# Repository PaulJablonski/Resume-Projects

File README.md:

# Projects
Projects that are a part of my independent studies accompanied by my resume.

**Currently Includes:**
1. ***Android Embedded Security System*** - Manual object-detecting Android application meant for security applications, detects, isolates, and labels people in camera feed utilizing manual DB-scanning, k-means color processing, and image calibration techniques.
2. ***Granular Synthesizer*** - Custom VST3 plugin that allows for the granularization of instruments and audio in DAWs. Capable of performing time-stretching, pitch adjustment, randomization, alongside adjusting dryness/wetness, grain size, and grain density.
3. ***FPGA Soccer Heads*** - A recreation of a classic flash game that incorporated SystemVerilog and C onto a Microblaze FPGA board that was connected to peripheral devices such as a monitor and keyboard.
4. ***Handwritten Text Recognition*** - Classifies single hand-illustrated character from user's input using SVM and convolution, where both the back-end and front-end were created from scratch using Python3 (Full Stack).
5. ***Illini Harmonics*** - A GCP-hosted music-based social web app made with SQL, React, and Python for rating your listening history and sharing it with friends.
6. ***Laser & Voice Assisted Cat Toy*** - Autonomous cat toy capable of collision avoidance, treat dispensing, catch detection, and audio-based commands. Involved PCB development, custom CAD modelling for the shell, and Arduino programming for the toy's behavioral state machine.

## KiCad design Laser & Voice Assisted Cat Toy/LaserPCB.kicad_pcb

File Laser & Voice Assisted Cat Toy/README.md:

# Laser & Voice Assisted Cat Toy

**Description:**

This project involves a mouse-like toy, which has been seen before, but is now refined with multiple more advanced systems. The primary sensors consist of a distance measuring laser, a vibrational sensor, and a microphone in tandem with a miniature speaker. The first two serve in engaging the cat and improving both longevity and noise generation, whereas the final sensor system vastly improves user interaction through various voice commands. More specifically, the laser can be utilized to avoid collisions and detect ahead of the mouse, sparking movement changes that are more realistic for an animal. The vibrational sensor furthermore detects when the toy has been caught, which either dispenses a treat or plays dead depending on the toy's state. Finally, the aforementioned voice commands allow for the user to locate the toy at any time, or manually activate the toy itself without a need for physical contact.

Physically speaking, the non-rolling shape of a mouse also allows for more rigid and controllable movement. This is important for stabilizing the toy’s primary sensors and allows for greater reactivity to its environment and consequently less noisy behavior. The sensors as mentioned also are accompanied by several motorized and more physical systems. A moving tail is used to mimic the more excitatory behaviors of prey, making it more engaging than a typical toy's static tail. This is accompanied by faster motorized movements and more realistic movement states as is regulated by a microcontroller and stepper motor-driven wheel system. Further speaking, a latch can be controlled through a servo and used for dispensing treats from the back of the toy upon being caught. And finally, a rechargeable lithium ion battery is incorporated and regulated by a circuit protection system for easy re-usability.
 
The toy itself comprises four total subsystems:

* Sensor subsystem, including a VL53L1X laser sensor, an SW-420 vibration sensor, and a KY-038 sound sensor.
* Microcontroller subsystem, comprised of the ATmega328p, taking inputs from the sensor subsystem, and outputting to the motors and outputs subsystem.
* Motors and outputs subsystem, consisting of two Nema 17 short body motors, two SG90 servo motors, two A4988 stepper drivers, a PAM8302 sound amplifier, and one JSM 2.5mm speaker.
* Power subsystem, which has a 11.1V lithium-ion battery, three AZ1117 voltage regulators, and a CYT1091 button.

**Included Files:**

1. CAD - Includes all CAD files for the cat toy, including both versions of its main body, top and bottom panels, and its separate cover for treat dispensing that attaches to the toy's treat servo motor.
2. CatToyOverview.pdf - A comprehensive 26-page report that displays the results of this project, alongside more in-depth technical descriptions for each subsystem.
3. LaserPCB.kicad_pcb - KiCAD PCB file for the front-mounted PCB that contains the laser sensor.
4. MainPCB.kicad_pcb - KiCAD PCB file for the main system PCB that contains all other sensors and outputs, alongside the microcontroller and additional connections.
5. MainPCB.kicad_sch - KiCAD schematic file that compliments and provides the layed-out prototype for the aforementioned main PCB.
6. ToyFirmware.ino - Arduino code file that contains all states and operations of the toy's programmed behavior. This file serves as its primary state machine and is loaded onto the final version's ATmega328p controller.

**Demonstration Video (Click on image):**

<div align="center" style="position: relative; display: inline-block;">
  
</div>

**Honorable Mention Award:**

<p align="center">  
  Figure 1. Award for this project given by UIUC Professor Fang, placing within the top 7 projects among nearly 50 groups.
</p>

**Design Figures:**

<p align="center">  
  Figure 2. Initial concept sketch for the cat toy, including all intended functionalities.
</p>

<p align="center">  
  Figure 3. Initial concept render of disassembled front and back view of the toy.
</p>

<p align="center">  
  Figure 4. Finalized CAD model of the toy alongside its interior.
</p>

<p align="center">  
  Figure 5. Assembly of the final product, including buttons, sensors on the sides, holes for wheel mounts, power button, etc.
</p>

<p align="center">  
  Figure 6. Main PCB design, not including the connections made in final assembly.
</p>

<p align="center">  
  Figure 7. Laser PCB design, not including the connections made in final assembly.
</p>

<p align="center">  
  Figure 8. Functionality of motor operations in final toy, red LED representing directions, and green representing motor steps. Laser detection here demonstrates directional change.
</p>

<p align="center">  
  Figure 9. Vibration and treat dispensing functionality on display, treats are dispensed after three taps (catches).
</p>

**Block Diagrams:**

<p align="center">  
  Figure 10. Block diagram for overall subsystems and their connections.
</p>

<p align="center">  
  Figure 11. State machine that defines the general program behavior.
</p>

**Subsystem Schematic Figures:**

<p align="center">  
  Figure 12. Overall circuit schematic diagram.
</p>

<p align="center">  
  Figure 13. Sensor subsystem schematic diagram.
</p>

<p align="center">  
  Figure 14. Microcontroller subsystem schematic diagram.
</p>

<p align="center">  
  Figure 15. Motors & outputs subsystem schematic diagram.
</p>

<p align="center">  
  Figure 16. Power subsystem schematic diagram.
</p>

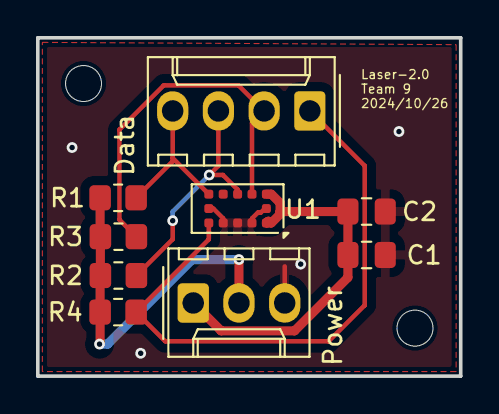
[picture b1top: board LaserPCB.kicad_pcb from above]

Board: 2 copper layers, 23.5 x 18.8 mm, 11 parts (0 on the bottom side), 7 nets.

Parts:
C1: 100nF; C_0805_2012Metric_Pad1.18x1.45mm_HandSolder
C2: 4.7uF; C_0805_2012Metric_Pad1.18x1.45mm_HandSolder
Data: Data; Molex_KK-254_AE-6410-04A_1x04_P2.54mm_Vertical
H1, H2: MountingHole; MountingHole_2mm
Power: Power; Molex_KK-254_AE-6410-03A_1x03_P2.54mm_Vertical
R1, R2, R3, R4: 10k; R_0805_2012Metric_Pad1.20x1.40mm_HandSolder
U1: VL53L1CXV0FY1; ST_VL53L1x

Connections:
/3.3V: C1.1, C2.1, Power.1, U1.1 (AVDDVCSEL), U1.11 (AVDD)
/GPIO1: Data.4, R1.2, U1.7 (GPIO1)
/IOVDD: Power.2, R1.1, R2.1, R3.1, R4.1
/SCL: Data.2, R3.2, U1.10 (SCL)
/SDA: Data.3, R2.2, U1.9 (SDA)
/XSHUT: Data.1, R4.2, U1.5 (XSHUT)
GND: C1.2, C2.2, Power.3, U1.2 (AVSSVCSEL), U1.3 (GND), U1.4 (GND), U1.6 (GND), U1.12 (GND)

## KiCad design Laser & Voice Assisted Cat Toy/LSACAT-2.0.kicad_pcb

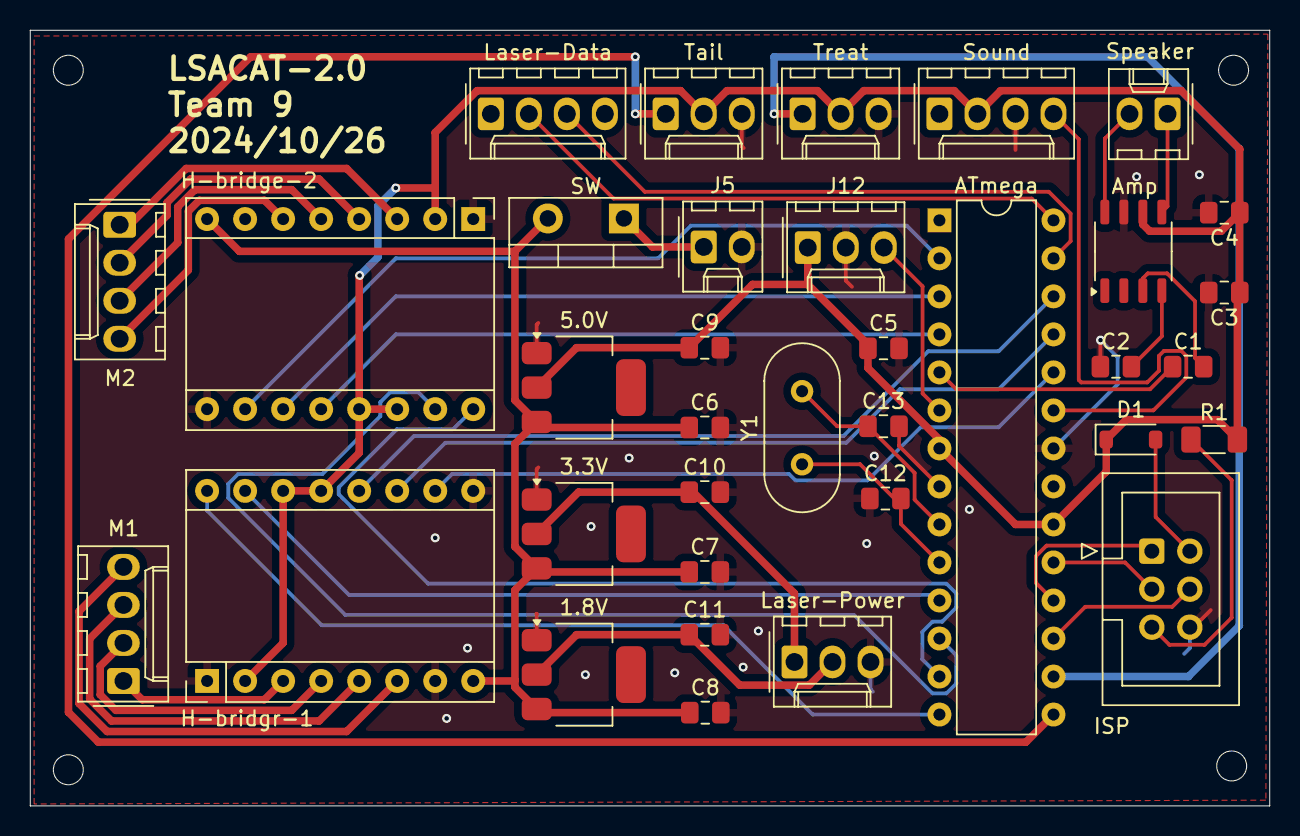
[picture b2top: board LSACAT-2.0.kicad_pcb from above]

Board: 2 copper layers, 82.8 x 51.8 mm, 39 parts (0 on the bottom side), 42 nets.

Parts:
1.8V: AZ1117-1.8; SOT-223
3.3V: AZ1117-3.3; SOT-223
5.0V: AZ1117-5.0; SOT-223
ATmega: ATmega328-P; DIP-28_W7.62mm
Amp: PAM8302AAS; SOP-8_3.9x4.9mm_P1.27mm
C1, C2: 0.1uF; C_0805_2012Metric_Pad1.18x1.45mm_HandSolder
C3: 10uF; C_0805_2012Metric_Pad1.18x1.45mm_HandSolder
C4, C5: 1uF; C_0805_2012Metric_Pad1.18x1.45mm_HandSolder
C6, C7, C8, C9, C10, C11: 22uF; C_0805_2012Metric_Pad1.18x1.45mm_HandSolder
C12, C13: 22pF; C_0805_2012Metric_Pad1.18x1.45mm_HandSolder
D1: MBR0520; D_SOD-123
H1, H2, H3, H4: MountingHole; MountingHole_2mm
H-bridge-2: A4988; Pololu_Breakout-16_15.2x20.3mm
H-bridgr-1: A4988; Pololu_Breakout-16_15.2x20.3mm
ISP: AVR-ISP-6; IDC-Header_2x03_P2.54mm_Vertical
J5: Battery; Molex_KK-254_AE-6410-02A_1x02_P2.54mm_Vertical
J12: SW-420; Molex_KK-254_AE-6410-03A_1x03_P2.54mm_Vertical
Laser-Data: Laser_Data; Molex_KK-254_AE-6410-04A_1x04_P2.54mm_Vertical
Laser-Power: Laser_Power; Molex_KK-254_AE-6410-03A_1x03_P2.54mm_Vertical
M1: M1; Molex_KK-254_AE-6410-04A_1x04_P2.54mm_Vertical
M2: M2; Molex_KK-254_AE-6410-04A_1x04_P2.54mm_Vertical
R1: 10k; R_1206_3216Metric_Pad1.30x1.75mm_HandSolder
SW: SW_Push; TO-220-2_Vertical
Sound: KY-038; Molex_KK-254_AE-6410-04A_1x04_P2.54mm_Vertical
Speaker: Speaker; Molex_KK-254_AE-6410-02A_1x02_P2.54mm_Vertical
Tail: Tail; Molex_KK-254_AE-6410-03A_1x03_P2.54mm_Vertical
Treat: Treat; Molex_KK-254_AE-6410-03A_1x03_P2.54mm_Vertical
Y1: 16Mhz; Crystal_HC49-U_Vertical

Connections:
/3.3V: 3.3V.2 (VO), C10.1, Laser-Power.1
/5V: 5.0V.2 (VO), ATmega.7 (VCC), ATmega.20 (AVCC), Amp.6 (VDD), C3.1, C4.1, C5.1, C9.1, D1.1 (K), H-bridge-2.2 (VDD), H-bridge-2.13 (~RESET), H-bridge-2.14 (~SLEEP), H-bridgr-1.2 (VDD), H-bridgr-1.13 (~RESET), H-bridgr-1.14 (~SLEEP), J12.1, R1.2, Sound.2, Tail.2, Treat.2
/11.1V: 1.8V.3 (VI), 3.3V.3 (VI), 5.0V.3 (VI), C6.1, C7.1, C8.1, H-bridge-2.8 (VMOT), H-bridgr-1.8 (VMOT), SW.2
/A1_M1: H-bridgr-1.4 (1A), M1.2
/A1_M2: H-bridge-2.4 (1A), M2.2
/A2_M1: H-bridgr-1.5 (2A), M1.3
/A2_M2: H-bridge-2.5 (2A), M2.3
/Anal_sound: ATmega.23 (PC0), Sound.4
/B1_M1: H-bridgr-1.3 (1B), M1.1
/B1_M2: H-bridge-2.3 (1B), M2.1
/B2_M1: H-bridgr-1.6 (2B), M1.4
/B2_M2: H-bridge-2.6 (2B), M2.4
/DIR_M1: ATmega.14 (PB0), H-bridgr-1.16 (DIR)
/DIR_M2: ATmega.13 (PD7), H-bridge-2.16 (DIR)
/IOVDD: 1.8V.2 (VO), C11.1, Laser-Power.2
/MISO: ATmega.18 (PB4), ISP.1 (MISO)
/MOSI: ATmega.17 (PB3), ISP.4 (MOSI)
/MS1_M1: ATmega.24 (PC1), H-bridgr-1.10 (MS1)
/MS1_M2: ATmega.2 (PD0), H-bridge-2.10 (MS1)
/MS2_M1: ATmega.25 (PC2), H-bridgr-1.11 (MS2)
/MS2_M2: ATmega.3 (PD1), H-bridge-2.11 (MS2)
/MS3_M1: ATmega.26 (PC3), H-bridgr-1.12 (MS3)
/MS3_M2: ATmega.4 (PD2), H-bridge-2.12 (MS3)
/PWM_Tail: ATmega.15 (PB1), Tail.1
/PWM_Treat: ATmega.16 (PB2), Treat.1
/SCK: ATmega.19 (PB5), ISP.3 (SCK)
/SCL: ATmega.28 (PC5), Laser-Data.2
/SDA: ATmega.27 (PC4), Laser-Data.3
/STEP_M1: ATmega.11 (PD5), H-bridgr-1.15 (STEP)
/STEP_M2: ATmega.12 (PD6), H-bridge-2.15 (STEP)
/Speaker_IN+: ATmega.5 (PD3), C1.1
/Speaker_O+: Amp.5 (OUT+), Speaker.1
/Speaker_O-: Amp.8 (OUT-), Speaker.2
/VIN: J5.1, SW.1
/Vout_Vibration: ATmega.6 (PD4), J12.3
GND: 1.8V.1 (GND), 3.3V.1 (GND), 5.0V.1 (GND), ATmega.8 (GND), ATmega.22 (GND), Amp.7 (GND), C2.1, C3.2, C4.2, C5.2, C6.2, C7.2, C8.2, C9.2, C10.2, C11.2, C12.1, C13.2, H-bridge-2.1 (GND), H-bridge-2.7 (GND), H-bridge-2.9 (~ENABLE), H-bridgr-1.1 (GND), H-bridgr-1.7 (GND), H-bridgr-1.9 (~ENABLE), ISP.6 (GND), J5.2, J12.2, Laser-Power.3, Sound.3, Tail.3, Treat.3
unnamed: D1.2 (A), ISP.2 (VCC)
unnamed: ISP.5 (~RST), R1.1
unnamed: Amp.3 (IN+), C1.2
unnamed: Amp.4 (IN-), C2.2
unnamed: ATmega.9 (XTAL1/PB6), C13.1, Y1.2
unnamed: ATmega.10 (XTAL2/PB7), C12.2, Y1.1

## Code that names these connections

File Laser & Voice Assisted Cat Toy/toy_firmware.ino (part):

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
// Assign pins to ATMega328P pinout
#define LED           0
#define Speaker_In    3  // --> pin 5  (PD3)
#define Vib_Out       4  // --> pin 6  (PD4)
#define STEP_M1       5  // --> pin 11 (PD5)
#define STEP_M2       6  // --> pin 12 (PD6)
#define DIR_M2        7  // --> pin 13 (PD7)
#define DIR_M1        8  // --> pin 14 (PB0)
#define PWM_Tail      9  // --> pin 15 (PB1)
#define PWM_Treat     10 // --> pin 16 (PB2)
#define Sound_Out     A0 // --> pin 23 (PC0)

// Create servo objects
Servo tailServo;
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
void setup() {
  // Set motor control pins as outputs
  pinMode(DIR_M1, OUTPUT);
  pinMode(DIR_M2, OUTPUT);
  pinMode(STEP_M1, OUTPUT);
  pinMode(STEP_M2, OUTPUT);
  pinMode(PWM_Tail, OUTPUT);
  pinMode(PWM_Treat, OUTPUT);
  pinMode(LED, OUTPUT);
  
  // Set sensor-related pins as inputs
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  pinMode(Vib_Out, INPUT);          

  // Other outputs
  tailServo.attach(PWM_Tail);       // Attach tail servo to its PIN
  treatServo.attach(PWM_Treat);     // Attach treat servo to its PIN
  pinMode(Speaker_In, OUTPUT);      // Speaker output
  Wire.begin();                     // I2C communication enabled for SDA and SCL pins automatically

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
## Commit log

2024-05-01 Rename README.md to README.md
2024-05-29 Added resume to project portfolio
2024-09-18 Rename FPGA Soccer Heads/font_rom.sv to FPGA Soccer Heads/ROM/font_rom.sv
2024-09-24 Resume.pdf
2024-09-24 Rename Jablonski Resume.pdf to Resume.pdf
2024-12-28 added android
2024-12-28 Rename toy_firmware.ino to ToyFirmware.ino
2025-01-02 Rename Cat Final Report.pdf to CatToyFinalReport.pdf
2025-04-22 Rename Granular Synth Overview.pdf to GranularSynthOverview.pdf
